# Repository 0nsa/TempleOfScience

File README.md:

# Temple of Science

The Temple of Science is an installation at Country Club 2018 in the two story
art cabin.  It combines projection and LEDs in a sychronized display.

The LEDs are leftovers from 
[Matt Mets' Crystal Archway](https://www.evilmadscientist.com/2013/making-at-maker-faire/)
they are housed in aluminum U-channel with diffuser. 

# Components

## SketchUp Model

The two story cabin is modeled in Design/ArtCabin.skp.  The LEDs are installed in
the cabin.  Once surface of each LED strip is colored a specific pink which is
picked up by the builder.

## Builder

The builder (Utilities/CC18ToSBuilder) takes the SketchUp model (converted to 
OBJ) and createsa Moonpaper compatible JSON file describing where in space the
LEDs are.

The builder is interactive.  Use the mouse to click on an LED strip and the
arrows to reorder until the strips are in the order appropriate for being 
addressed by the controllers. Press S to save.

## Simulator

The simulator lives under Utilities/CC18ToSSimulator.  Run it and the 
transmitter to get a preview of the installation.

The simulator also takes frames from [Syphon](http://syphon.v002.info) and
displays them on the front of the cabin.

## Transmitter

The transmitter (Routines/CC18ToSTransmitter) runs a single routine that takes
frames from [Syphon](http://syphon.v002.info) and maps them to the LEDs.

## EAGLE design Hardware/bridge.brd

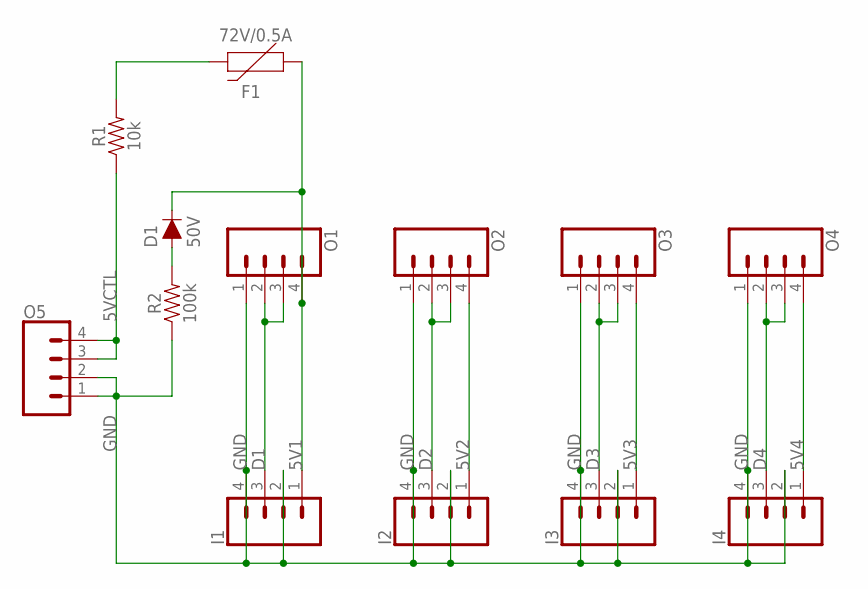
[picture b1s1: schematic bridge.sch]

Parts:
D1: 50V; DIODE-1N4001
F1: 72V/0.5A; PTH
I1, I2, I3, I4: CONN_04SCREW; SCREWTERMINAL-3.5MM-4
O1, O2, O3, O4, O5: CONN_04SCREW; SCREWTERMINAL-3.5MM-4
R1: 10k; AXIAL-0.3
R2: 100k; AXIAL-0.3

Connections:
5V1: D1.C, F1.P$1 (1), I1.1, O1.4
5V2: I2.1, O2.4
5V3: I3.1, O3.4
5V4: I4.1, O4.4
5VCTL: O5.3, O5.4, R1.P$1 (1)
D1: I1.3, O1.2, O1.3
D2: I2.3, O2.2, O2.3
D3: I3.3, O3.2, O3.3
D4: I4.3, O4.2, O4.3
GND: I1.2, I1.4, I2.2, I2.4, I3.2, I3.4, I4.2, I4.4, O1.1, O2.1, O3.1, O4.1, O5.1, O5.2, R2.P$1 (1)
unnamed: F1.P$2 (2), R1.P$2 (2)
unnamed: D1.A, R2.P$2 (2)

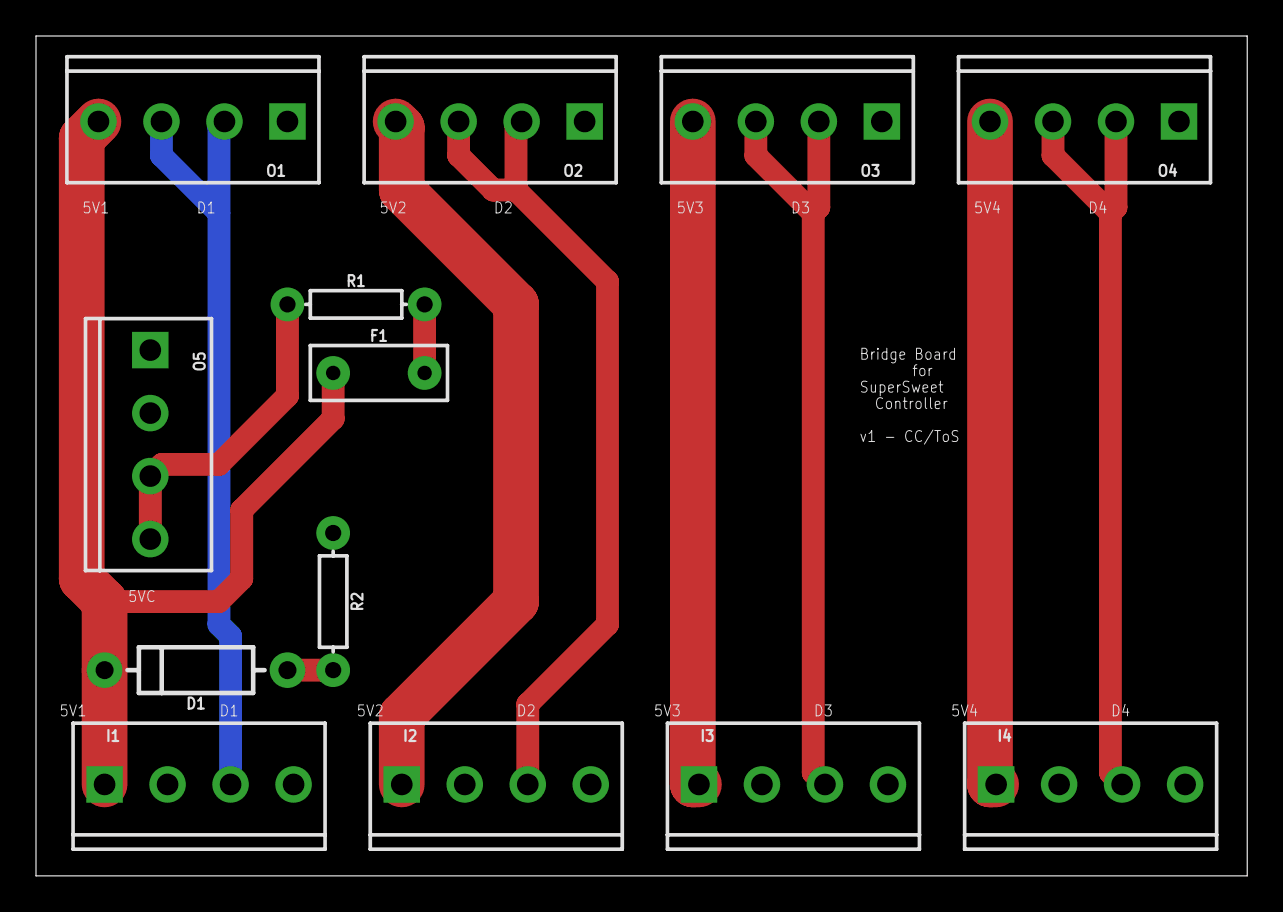
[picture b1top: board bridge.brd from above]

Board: 2 copper layers, 67.3 x 46.7 mm, 13 parts (0 on the bottom side), 12 nets.

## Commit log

2018-04-28 Added photo
2018-04-28 Added cabin photo, trying titles
2018-05-22 Current state

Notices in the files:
parts and their libraries:
SparkFun-Connectors: Licensing: Creative Commons ShareAlike 4.0 International - https://creativecommons.org/licenses/by-sa/4.0
